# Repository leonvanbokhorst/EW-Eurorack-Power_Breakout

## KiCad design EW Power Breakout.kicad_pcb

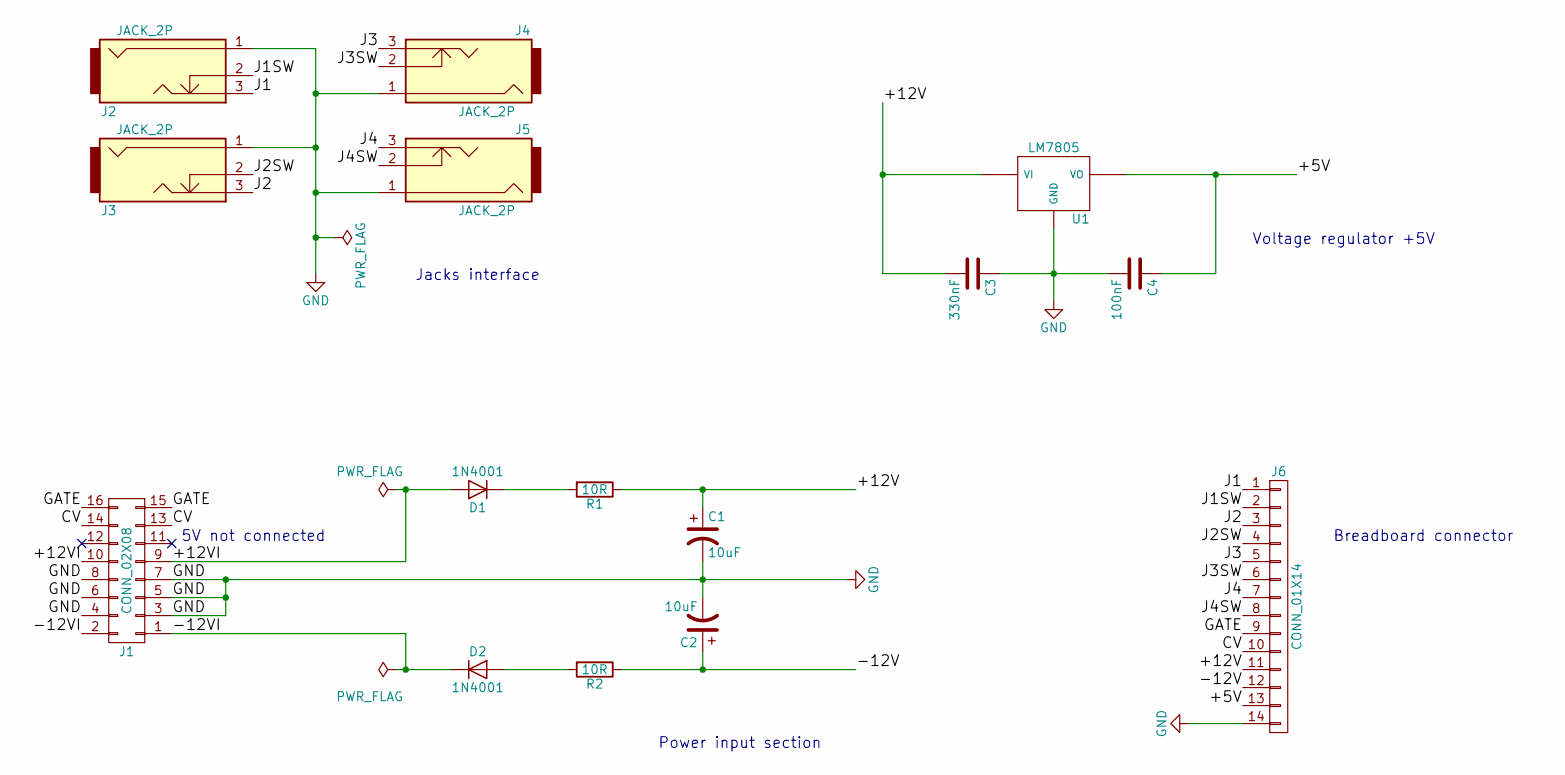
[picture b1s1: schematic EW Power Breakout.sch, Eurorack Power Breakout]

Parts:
C1, C2: 10uF; CP_Radial_D5.0mm_P2.00mm
C3: 330nF; C_Disc_D6.0mm_W4.4mm_P5.00mm
C4: 100nF; C_Disc_D6.0mm_W4.4mm_P5.00mm
D1, D2: 1N4001; D_DO-41_SOD81_P12.70mm_Horizontal
J1: CONN_02X08; IDC_Header_Straight_16pins
J2, J3, J4, J5: JACK_2P; PJ301M-12
J6: CONN_01X14; Pin_Header_Straight_1x14_Pitch2.54mm
R1, R2: 10R; R_Axial_DIN0207_L6.3mm_D2.5mm_P10.16mm_Horizontal
U1: LM7805; TO-220_Vertical

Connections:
/+5V: C4.1, J6.13, U1.3 (VO)
/+12V: C1.1, C3.2, J6.11, R1.1, U1.1 (VI)
/+12VI: D1.2 (A), J1.9, J1.10
/-12V: C2.1, J6.12, R2.1
/-12VI: D2.1 (K), J1.1, J1.2
/CV: J1.13, J1.14, J6.10
/GATE: J1.15, J1.16, J6.9
/J1: J2.3, J6.1
/J1SW: J2.2, J6.2
/J2: J3.3, J6.3
/J2SW: J3.2, J6.4
/J3: J4.3, J6.5
/J3SW: J4.2, J6.6
/J4: J5.3, J6.7
/J4SW: J5.2, J6.8
GND: C1.2, C2.2, C3.1, C4.2, J1.3, J1.4, J1.5, J1.6, J1.7, J1.8, J2.1, J3.1, J4.1, J5.1, J6.14, U1.2 (GND)
unnamed: D1.1 (K), R1.2
unnamed: D2.2 (A), R2.2

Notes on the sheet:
5V not connected
Voltage regulator +5V
Breadboard connector
Jacks interface
Power input section

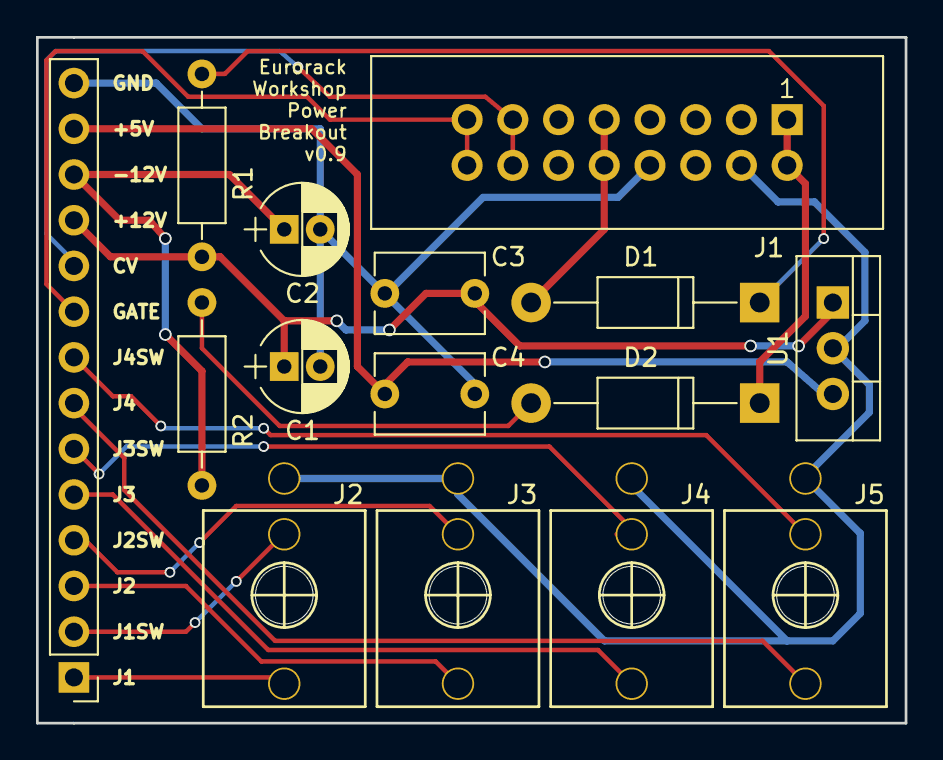
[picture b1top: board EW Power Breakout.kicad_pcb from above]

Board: 2 copper layers, 48.3 x 38.1 mm, 15 parts (0 on the bottom side), 18 nets.

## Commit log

2017-08-22 First commit after init
2017-08-22 Jacks and labels
2017-08-22 Schematic done
2017-08-22 Component associations made
2017-08-22 Netlist added
2017-08-22 Component placement on PCB (rough)
2017-08-24 Fixed IDC routing bug
2017-08-24 Drills in PJ301M-12 jacks
2017-08-24 Removed corrupt logo mod
2017-08-25 Design change. Connector to the left
2017-08-25 Wiring PCB
2017-08-25 GND copper fill
2017-08-25 Gerber files added
2017-08-26 New gerbers with extended info
